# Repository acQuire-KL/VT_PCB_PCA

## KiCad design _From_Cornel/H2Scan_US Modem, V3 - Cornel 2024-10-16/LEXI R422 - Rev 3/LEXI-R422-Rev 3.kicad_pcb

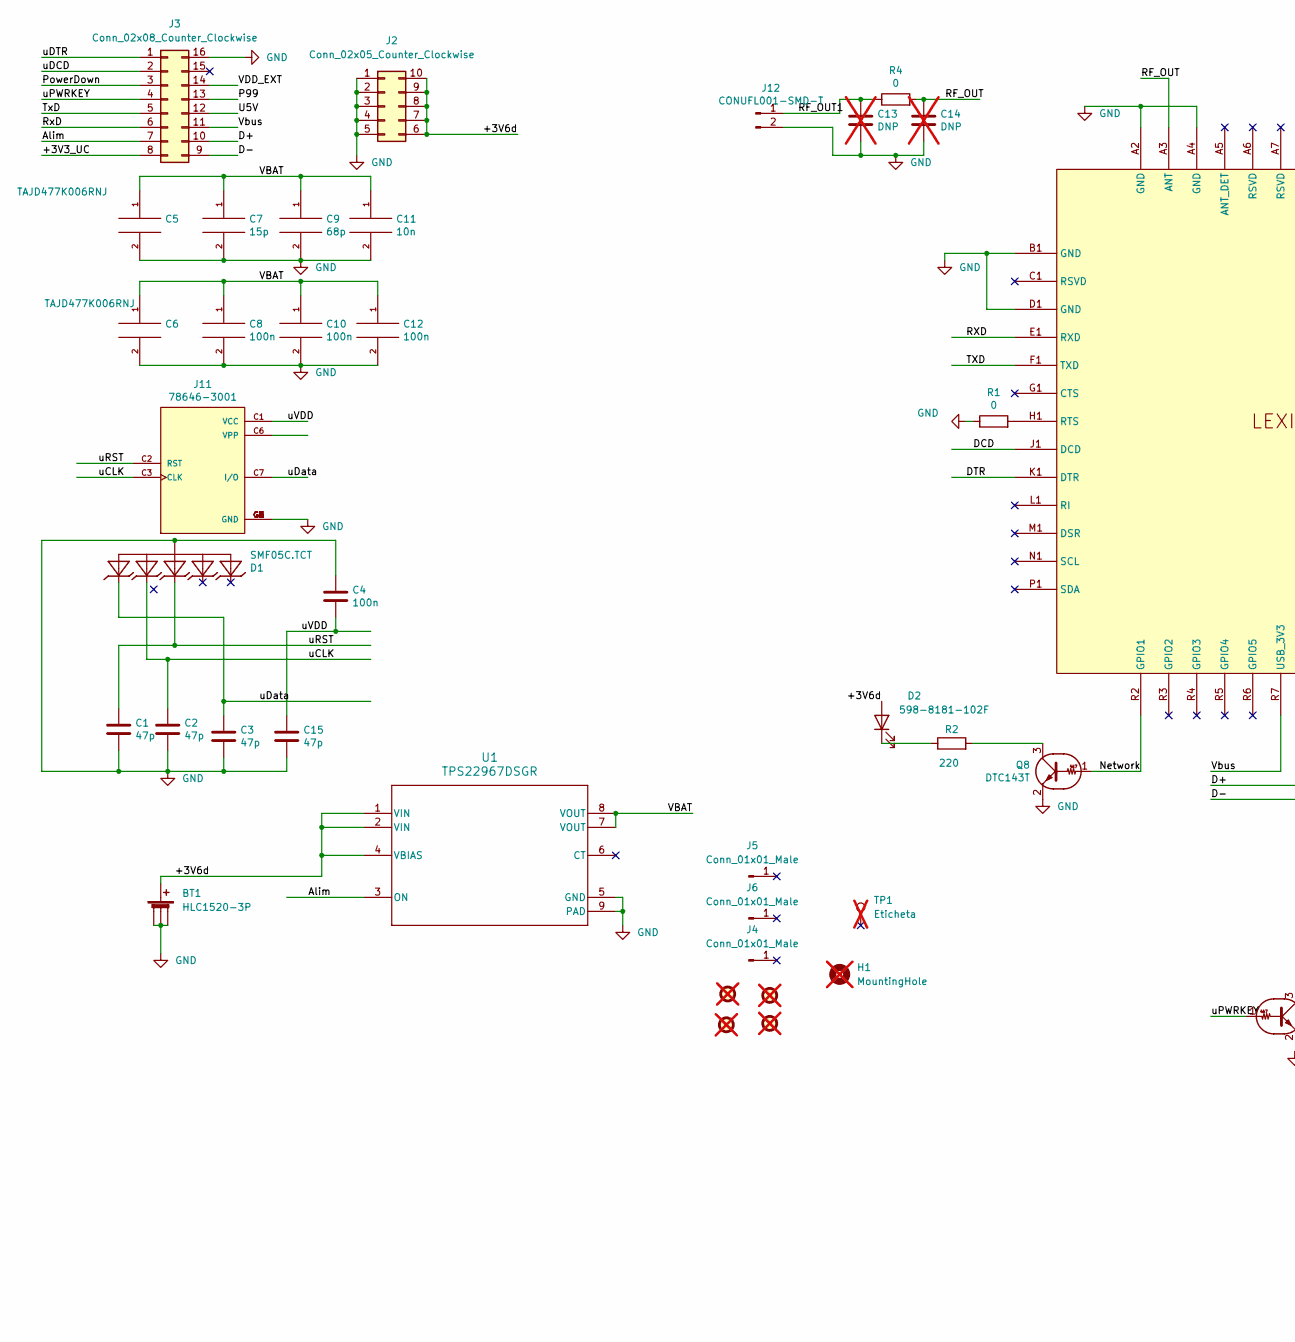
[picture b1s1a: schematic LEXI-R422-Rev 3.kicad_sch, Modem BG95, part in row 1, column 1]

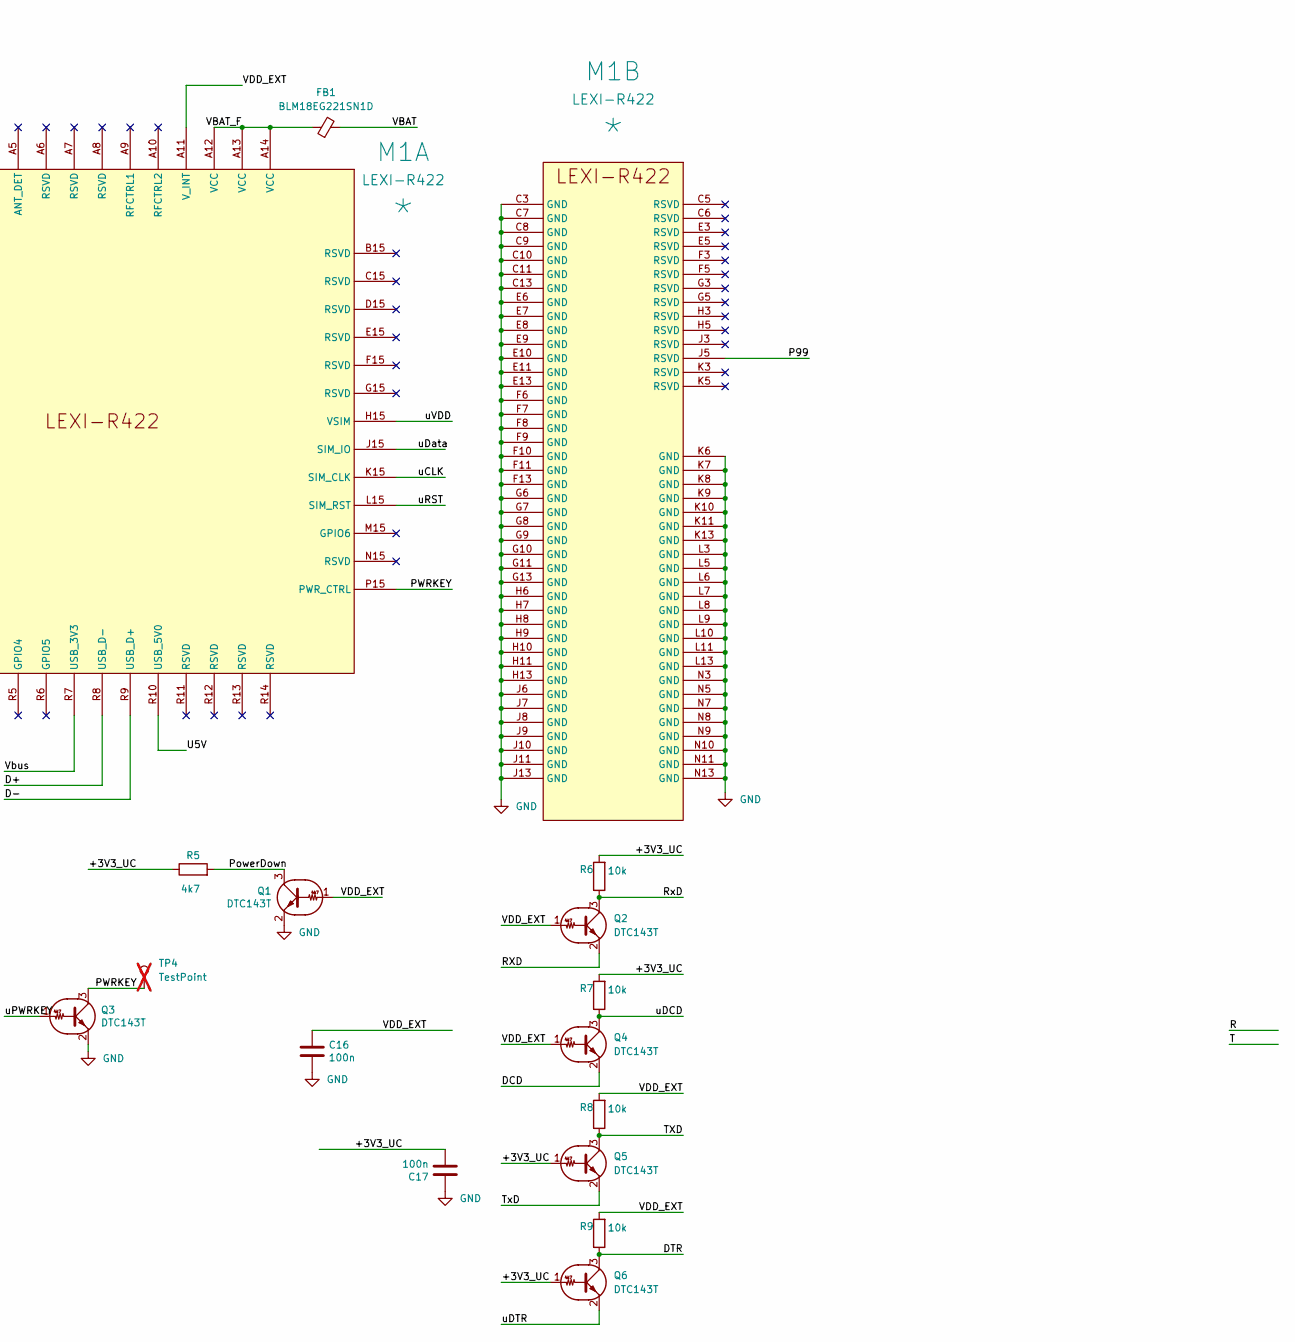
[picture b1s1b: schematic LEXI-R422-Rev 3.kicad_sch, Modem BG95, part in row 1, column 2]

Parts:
BT1: HLC1520-3P
C1, C2, C3, C15: 47p; C_0603_1608Metric
C4, C8, C10, C12, C16, C17: 100n; C_0603_1608Metric
C5, C6: TAJD477K006RNJ; CP_EIA-7361-38_AVX-V_Pad2.18x3.30mm_HandSolder
C7: 15p; C_0603_1608Metric
C9: 68p; C_0603_1608Metric
C11: 10n; C_0603_1608Metric
C13, C14: DNP; C_0603_1608Metric; not fitted
D1: SMF05C.TCT; SC70-6
D2: 598-8181-102F; LED_0805_2012Metric
FB1: BLM18EG221SN1D; L_Walsin_WLFM201209x
FID1, FID2, FID3, FID4: Fiducial; Fiducial_1mm_Mask2mm; not fitted
H1: MountingHole; MountingHole_2.5mm Simpla; not fitted
J2: Conn_02x05_Counter_Clockwise; PinHeader_2x05_P2.54mm_Vertical_SMD_MOD
J3: Conn_02x08_Counter_Clockwise; PinHeader_2x08_P2.54mm_Vertical_SMD_MOD
J4, J5, J6: Conn_01x01_Male; TestPoint_Pad_5.1x5.1mm
J11: 78646-3001; MOLEX_78646-3001; DIGI-KEY_PART_NUMBER WM9364CT-ND
J12: CONUFL001-SMD-T; U.FL_Molex_MCRF_73412-0110_Vertical
M1: LEXI-R422; LEXI; Manufacturer P/N *
Q1, Q2, Q3, Q4, Q5, Q6, Q8: DTC143T; SOT-23
R1, R4: 0; R_0603_1608Metric
R2: 220; R_0603_1608Metric
R5: 4k7; R_0603_1608Metric
R6, R7, R8, R9: 10k; R_0603_1608Metric
TP1: Eticheta; not fitted
TP4: TestPoint; TestPoint_Pad_D1.5mm; not fitted
U1: TPS22967DSGR; WSON-8-1EP_2x2mm_P0.5mm_EP0.9x1.6mm_ThermalVias

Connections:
/+3V3_UC: C17.2, J3.8, Q5.1 (B), Q6.1 (B), R5.1, R6.2, R7.2
/+3V6d: BT1.1 (+), D2.2 (A), J2.6, J2.7, J2.8, J2.9, J2.10, U1.1 (VIN), U1.2 (VIN), U1.4 (VBIAS)
/Alim: J3.7, U1.3 (ON)
/D+: J3.10, M1.R8 (USB_D-)
/D-: J3.9, M1.R9 (USB_D+)
/DCD: M1.J1 (DCD), Q4.2 (E)
/DTR: M1.K1 (DTR), Q6.3 (C), R9.1
/Network: M1.R2 (GPIO1), Q8.1 (B)
/P99: J3.13, M1.J5 (RSVD)
/PWRKEY: M1.P15 (PWR_CTRL), Q3.3 (C), TP4.1
/PowerDown: J3.3, Q1.3 (C), R5.2
/RF_OUT: C14.1, M1.A3 (ANT), R4.2
/RF_OUT1: C13.1, J12.1, R4.1
/RXD: M1.E1 (RXD), Q2.2 (E)
/RxD: J3.6, Q2.3 (C), R6.1
/TXD: M1.F1 (TXD), Q5.3 (C), R8.1
/TxD: J3.5, Q5.2 (E)
/U5V: J3.12, M1.R10 (USB_5V0)
/VBAT: C5.1, C6.1, C7.1, C8.1, C9.1, C10.1, C11.1, C12.1, FB1.2, U1.7 (VOUT), U1.8 (VOUT)
/VBAT_F: FB1.1, M1.A12 (VCC), M1.A13 (VCC), M1.A14 (VCC)
/VDD_EXT: C16.1, J3.14, M1.A11 (V_INT), Q1.1 (B), Q2.1 (B), Q4.1 (B), R8.2, R9.2
/Vbus: J3.11, M1.R7 (USB_3V3)
/uCLK: C2.1, D1.5, J11.C3 (CLK), M1.K15 (SIM_CLK)
/uDCD: J3.2, Q4.3 (C), R7.1
/uDTR: J3.1, Q6.2 (E)
/uData: C3.1, D1.6, J11.C7 (I/O), M1.J15 (SIM_IO)
/uPWRKEY: J3.4, Q3.1 (B)
/uRST: C1.1, D1.4, J11.C2 (RST), M1.L15 (SIM_RST)
/uVDD: C4.2, C15.1, J11.C1 (VCC), M1.H15 (VSIM)
GND: BT1.2 (-), BT1.3 (-), BT1.4 (-), C1.2, C2.2, C3.2, C4.1, C5.2, C6.2, C7.2, C8.2, C9.2, C10.2, C11.2, C12.2, C13.2, C14.2, C15.2, C16.2, C17.1, D1.2, J2.1, J2.2, J2.3, J2.4, J2.5, J3.16, J11.C5 (GND), J11.G1 (GND), J11.G2 (GND), J11.G3 (GND), J11.G4 (GND), J11.G5 (GND), J11.G6 (GND), J12.2, M1.A2 (GND), M1.A4 (GND), M1.B1 (GND), M1.C3 (GND), M1.C7 (GND), M1.C8 (GND), M1.C9 (GND), M1.C10 (GND), M1.C11 (GND), M1.C13 (GND), M1.D1 (GND), M1.E6 (GND), M1.E7 (GND), M1.E8 (GND), M1.E9 (GND), M1.E10 (GND), M1.E11 (GND), M1.E13 (GND), M1.F6 (GND), M1.F7 (GND), M1.F8 (GND), M1.F9 (GND), M1.F10 (GND), M1.F11 (GND), M1.F13 (GND), M1.G6 (GND), M1.G7 (GND), M1.G8 (GND), M1.G9 (GND), M1.G10 (GND), M1.G11 (GND), M1.G13 (GND), M1.H6 (GND), M1.H7 (GND), M1.H8 (GND), M1.H9 (GND), M1.H10 (GND), M1.H11 (GND), M1.H13 (GND), M1.J6 (GND), M1.J7 (GND), M1.J8 (GND), M1.J9 (GND), M1.J10 (GND), M1.J11 (GND), M1.J13 (GND), M1.K6 (GND), M1.K7 (GND), M1.K8 (GND), M1.K9 (GND), M1.K10 (GND), M1.K11 (GND), M1.K13 (GND), M1.L3 (GND), M1.L5 (GND), M1.L6 (GND), M1.L7 (GND), M1.L8 (GND), M1.L9 (GND), M1.L10 (GND), M1.L11 (GND), M1.L13 (GND), M1.N3 (GND), M1.N5 (GND), M1.N7 (GND), M1.N8 (GND), M1.N9 (GND), M1.N10 (GND), M1.N11 (GND), M1.N13 (GND), Q1.2 (E), Q3.2 (E), Q8.2 (E), R1.1, U1.5 (GND), U1.9 (PAD)
unnamed: D2.1 (K), R2.1
unnamed: M1.H1 (RTS), R1.2
unnamed: Q8.3 (C), R2.2

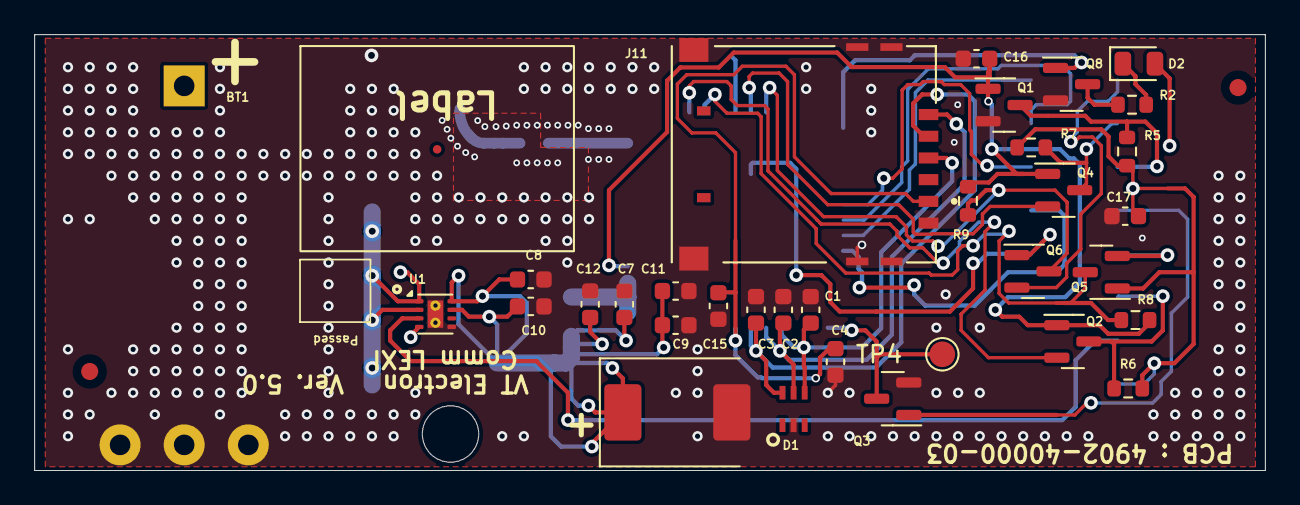
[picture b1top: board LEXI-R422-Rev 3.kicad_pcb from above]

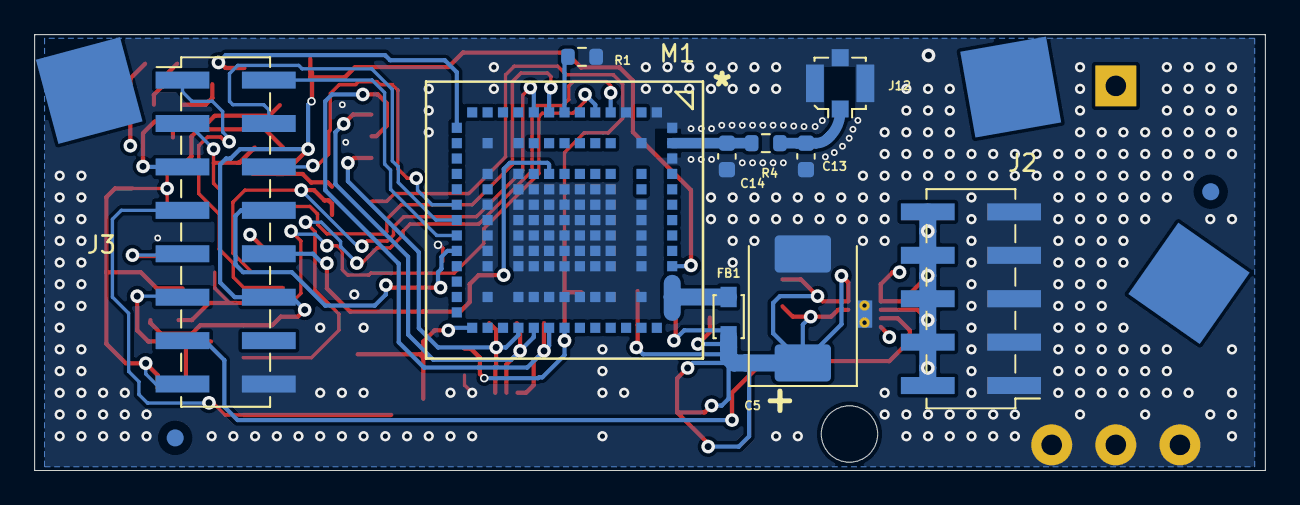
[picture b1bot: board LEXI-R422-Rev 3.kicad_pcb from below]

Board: 4 copper layers, 72.0 x 25.5 mm, 52 parts (15 on the bottom side), 33 nets.

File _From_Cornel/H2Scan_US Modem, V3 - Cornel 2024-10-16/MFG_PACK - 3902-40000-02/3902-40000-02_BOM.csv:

"Reference","Value","Datasheet","Footprint","Qty","DNP","VTPN"
"BT1","HLC1520-3P","~","Battery:HLC1520-3P","1","","4200-00020-00"
"C1,C2,C3,C15","47p","~","Capacitor_SMD:C_0603_1608Metric","4","","4106-00080-00"
"C4,C8,C10,C12,C16,C17","100n","~","Capacitor_SMD:C_0603_1608Metric","6","","4106-00020-00"
"C5,C6","TAJD477K006RNJ","~","Capacitor_Tantalum_SMD:CP_EIA-7361-38_AVX-V_Pad2.18x3.30mm_HandSolder","2","","4128-00100-00"
"C7","15p","~","Capacitor_SMD:C_0603_1608Metric","1","","4106-00070-00"
"C9","68p","~","Capacitor_SMD:C_0603_1608Metric","1","","4106-00060-00"
"C11","10n","~","Capacitor_SMD:C_0603_1608Metric","1","","4106-00015-00"
"C13,C14","DNP","~","Capacitor_SMD:C_0603_1608Metric","2","DNP","4106-00000-00"
"D1","SMF05C.TCT","","Diode_SMD:SC70-6","1","","4724-00010-00"
"D2","598-8181-102F","~","LED_SMD:LED_0805_2012Metric","1","","4752-01010-00"
"FB1","BLM18EG221SN1D","~","Inductor_SMD:L_Walsin_WLFM201209x","1","","4300-01010-00"
"FID1,FID2,FID3,FID4","Fiducial","~","Fiducial:Fiducial_1mm_Mask2mm","4","DNP","4000-00000-00"
"H1","MountingHole","~","MountingHole:MountingHole_2.5mm  Simpla","1","DNP","4000-00000-00"
"J2","Conn_02x05_Counter_Clockwise","~","Connector_PinHeader_2.54mm:PinHeader_2x05_P2.54mm_Vertical_SMD_MOD","1","","4402-00020-00"
"J3","Conn_02x08_Counter_Clockwise","~","Connector_PinHeader_2.54mm:PinHeader_2x08_P2.54mm_Vertical_SMD_MOD","1","","4402-00030-00"
"J4,J5,J6","Conn_01x01_Male","~","TestPoint:TestPoint_Pad_5.1x5.1mm","3","","4753-00010-00"
"J11","78646-3001","","Connector_Molex:MOLEX_78646-3001","1","","4414-00020-00"
"J12","CONUFL001-SMD-T","~","Connector_Coaxial:U.FL_Molex_MCRF_73412-0110_Vertical","1","","4416-00010-00"
"M1","LEXI-R422","","ublox:LEXI","1","","4716-00020-00"
"Q1,Q2,Q3,Q4,Q5,Q6,Q8","DTC143T","","Package_TO_SOT_SMD:SOT-23","7","","4500-00010-00"
"R1,R4","0","~","Resistor_SMD:R_0603_1608Metric","2","","4006-00001-00"
"R2","220","~","Resistor_SMD:R_0603_1608Metric","1","","4006-00020-00"
"R5","4k7","~","Resistor_SMD:R_0603_1608Metric","1","","4006-00150-00"
"R6,R7,R8,R9","10k","~","Resistor_SMD:R_0603_1608Metric","4","","4006-00170-00"
"TP1","Eticheta","~","Symbol:Eticheta","1","DNP","4000-00000-00"
"TP4","TestPoint","~","TestPoint:TestPoint_Pad_D1.5mm","1","DNP","4000-00000-00"
"U1","TPS22967DSGR","TPS22967DSGR","Package_SON:WSON-8-1EP_2x2mm_P0.5mm_EP0.9x1.6mm_ThermalVias","1","","4702-01010-00"

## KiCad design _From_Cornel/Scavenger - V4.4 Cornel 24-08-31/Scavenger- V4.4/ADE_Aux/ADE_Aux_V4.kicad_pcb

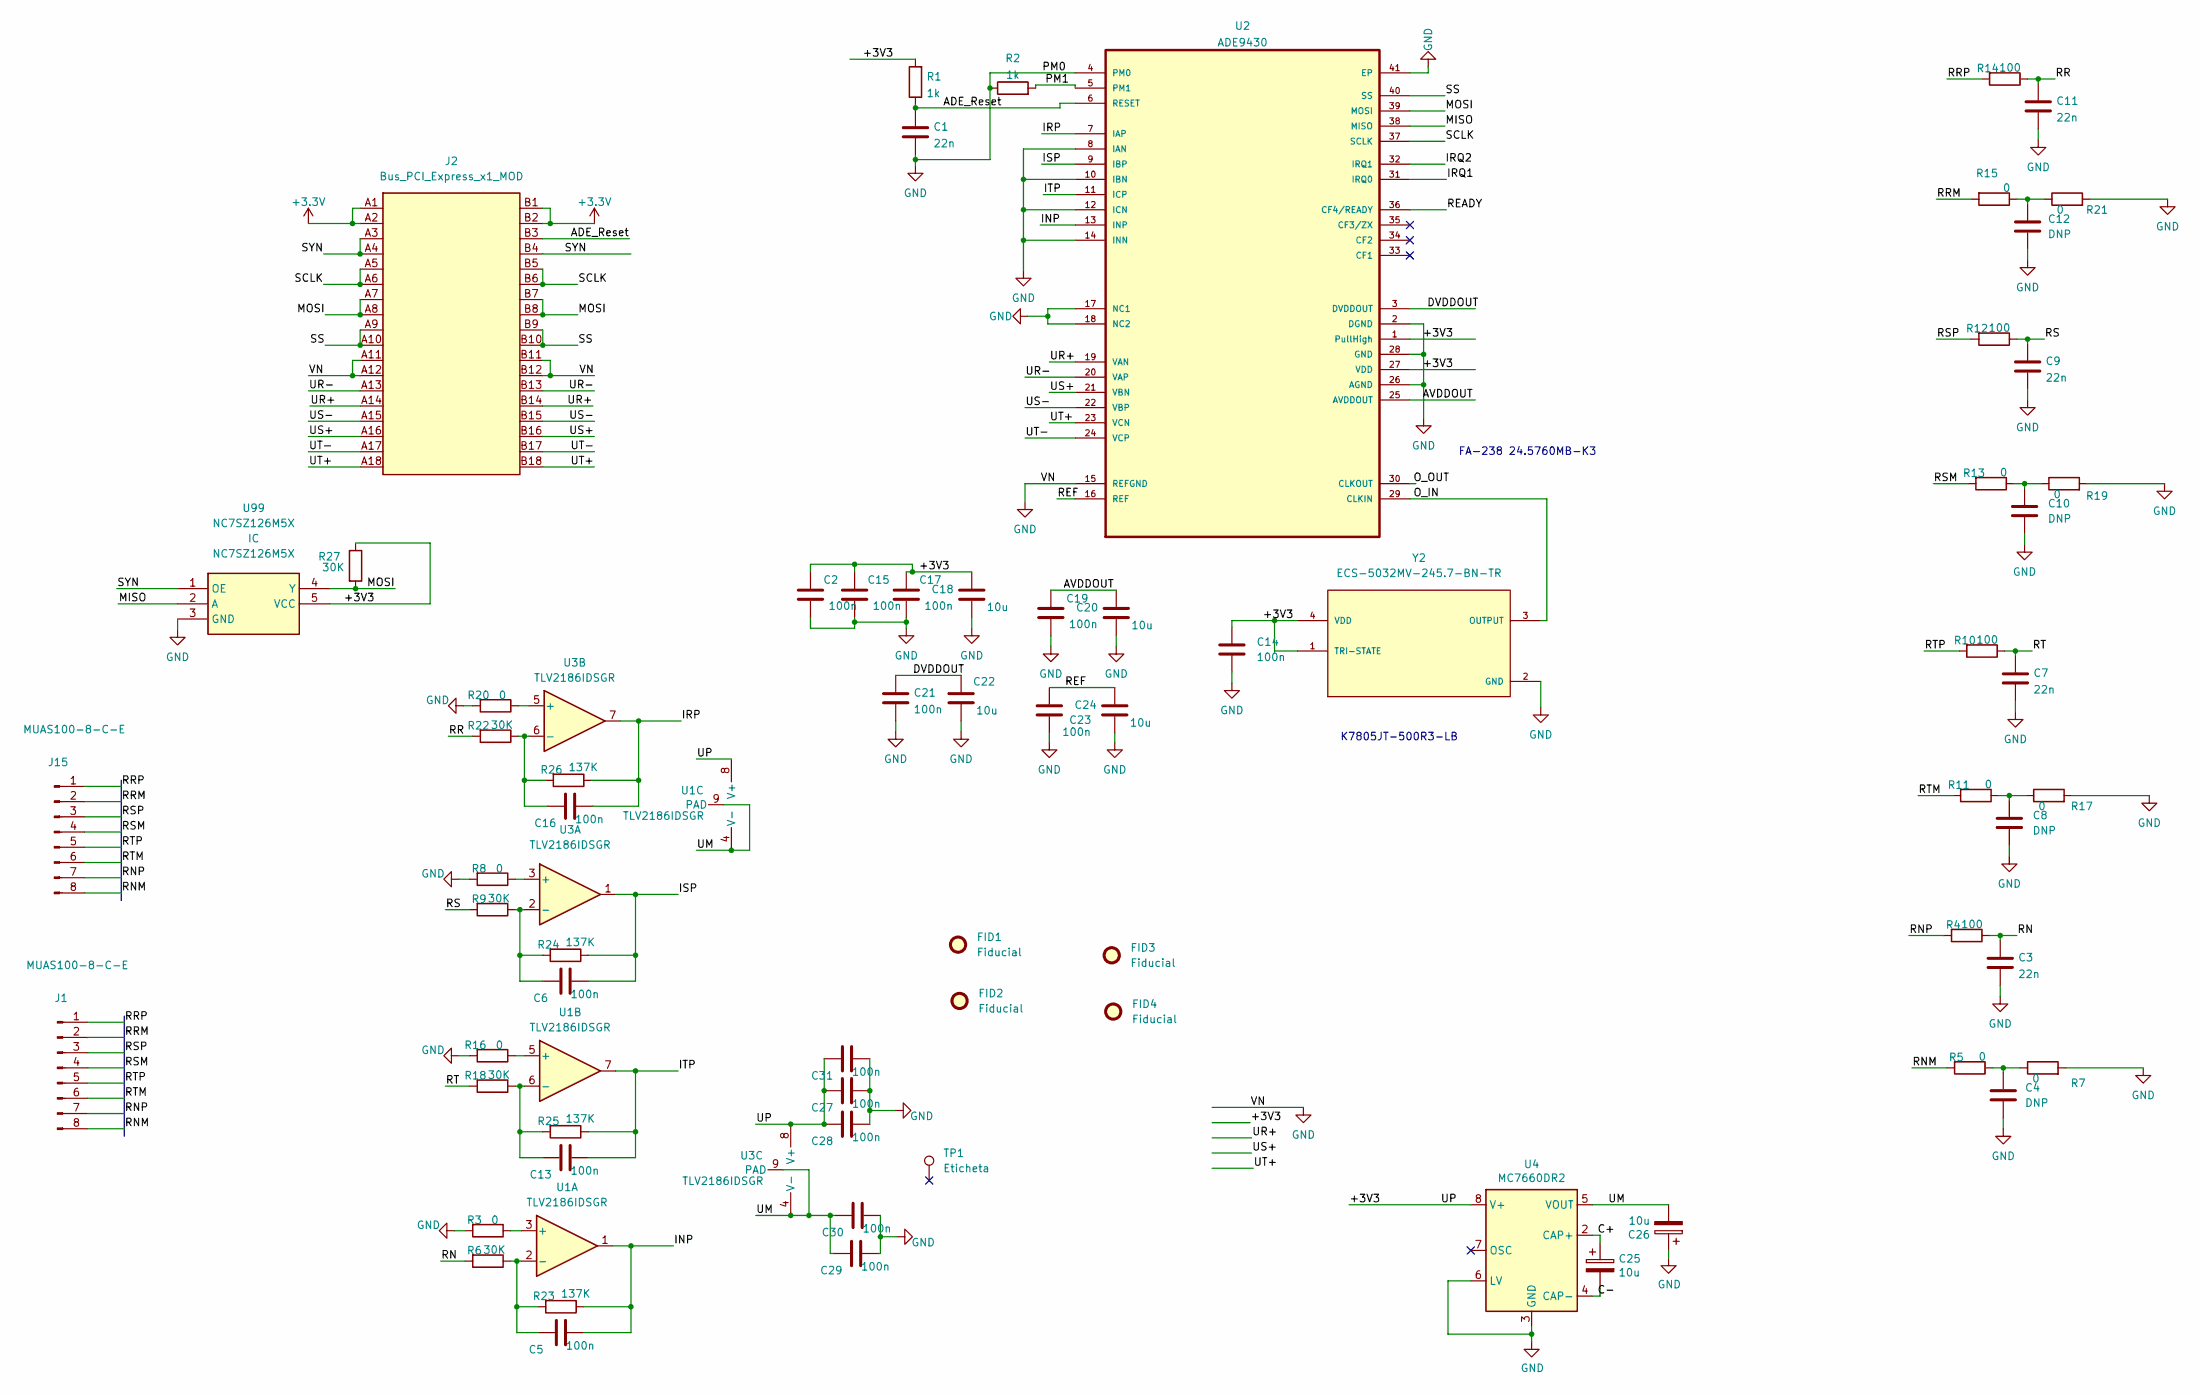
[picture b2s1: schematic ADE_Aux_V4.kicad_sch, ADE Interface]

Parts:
C1, C3, C7, C9, C11: 22n; C_0402_1005Metric
C2: 100n; C_0603_1608Metric
C4, C8, C10, C12: DNP; C_0402_1005Metric
C5, C6, C13, C14, C15, C16, C17, C19, C21, C23, C27, C28, C29, C30, C31: 100n; C_0402_1005Metric
C18, C20, C22, C24, C25, C26: 10u; C_1206_3216Metric
FID1, FID2, FID3, FID4: Fiducial; Fiducial_1mm_Mask2mm
J1: MUAS100-8-C-E; A2501-SR08-XH8AWB
J2: Bus_PCI_Express_x1_MOD; BUS_PCIexpress_x1
J15: MUAS100-8-C-E; PinHeader_1x08_P2.54mm_Vertical
R1, R2: 1k; R_0402_1005Metric
R3, R5, R7, R8, R11, R13, R15, R16, R17, R19, R20, R21: 0; R_0402_1005Metric
R4, R10, R12, R14: 100; R_0402_1005Metric
R6, R9, R18, R22, R27: 30K; R_0402_1005Metric
R23, R24, R25, R26: 137K; R_0402_1005Metric
TP1: Eticheta
U1, U3: TLV2186IDSGR; WSON-8-1EP_2x2mm_P0.5mm_EP0.9x1.6mm_ThermalVias
U2: ADE9430; MPN AD9115BCPZ
U4: MC7660DR2; SO-8_3.9x4.9mm_P1.27mm
U99: NC7SZ126M5X; Buffer3S; Manufacturer_Part_Number NC7SZ126M5X; Mouser Part Number 512-NC7SZ126M5X
Y2: ECS-5032MV-245.7-BN-TR; OSC_ECS-5032MV-245.7-BN-TR

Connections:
/ADE_Reset: C1.1, J2.B3, R1.1, U2.6 (RESET)
/AVDDOUT: C19.1, C20.1, U2.25 (AVDDOUT)
/C+: C25.1, U4.2 (CAP+)
/C-: C25.2, U4.4 (CAP-)
/DVDDOUT: C21.1, C22.1, U2.3 (DVDDOUT)
/INP: C5.1, R23.1, U1.1, U2.13 (INP)
/IRP: C16.1, R26.1, U2.7 (IAP), U3.7
/IRQ1: U2.31 (IRQ0)
/IRQ2: U2.32 (IRQ1)
/ISP: C6.1, R24.1, U2.9 (IBP), U3.1
/ITP: C13.1, R25.1, U1.7, U2.11 (ICP)
/MISO: U2.38 (MISO), U99.2 (A)
/MOSI: J2.A7, J2.A8, J2.B7, J2.B8, R27.2, U2.39 (MOSI), U99.4 (Y)
/O_IN: U2.29 (CLKIN), Y2.3 (OUTPUT)
/O_OUT: U2.30 (CLKOUT)
/PM1: R2.2, U2.5 (PM1)
/READY: U2.36 (CF4/READY)
/REF: C23.1, C24.1, U2.16 (REF)
/RN: C3.1, R4.1, R6.2
/RNM: J1.8, J15.8, R5.2
/RNP: J1.7, J15.7, R4.2
/RR: C11.1, R14.1, R22.2
/RRM: J1.2, J15.2, R15.2
/RRP: J1.1, J15.1, R14.2
/RS: C9.1, R9.2, R12.1
/RSM: J1.4, J15.4, R13.2
/RSP: J1.3, J15.3, R12.2
/RT: C7.1, R10.1, R18.2
/RTM: J1.6, J15.6, R11.2
/RTP: J1.5, J15.5, R10.2
/SCLK: J2.A5, J2.A6, J2.B5, J2.B6, U2.37 (SCLK)
/SS: J2.A9, J2.A10, J2.B9, J2.B10, U2.40 (SS)
/SYN: J2.A3, J2.A4, J2.B4, U99.1 (OE)
/UM: C26.2, C29.2, C30.2, U1.4 (V-), U1.9 (PAD), U3.4 (V-), U3.9 (PAD), U4.5 (VOUT)
/UR+: J2.A14, J2.B14, U2.19 (VAN)
/UR-: J2.A13, J2.B13, U2.20 (VAP)
/US+: J2.A16, J2.B16, U2.21 (VBN)
/US-: J2.A15, J2.B15, U2.22 (VBP)
/UT+: J2.A18, J2.B18, U2.23 (VCN)
/UT-: J2.A17, J2.B17, U2.24 (VCP)
GND: C1.2, C2.2, C3.2, C4.2, C7.2, C8.2, C9.2, C10.2, C11.2, C12.2, C14.2, C15.2, C17.2, C18.2, C19.2, C20.2, C21.2, C22.2, C23.2, C24.2, C26.1, C27.1, C28.1, C29.1, C30.1, C31.1, J2.A11, J2.A12, J2.B11, J2.B12, R2.1, R3.2, R7.2, R8.2, R16.2, R17.2, R19.2, R20.2, R21.2, U2.2 (DGND), U2.4 (PM0), U2.8 (IAN), U2.10 (IBN), U2.12 (ICN), U2.14 (INN), U2.15 (REFGND), U2.17 (NC1), U2.18 (NC2), U2.26 (AGND), U2.28 (GND), U2.41 (EP), U4.3 (GND), U4.6 (LV), U99.3 (GND), Y2.2 (GND)
unnamed: C4.1, R5.1, R7.1
unnamed: C5.2, R6.1, R23.2, U1.2 (-)
unnamed: C6.2, R9.1, R24.2, U3.2 (-)
unnamed: C8.1, R11.1, R17.1
unnamed: C10.1, R13.1, R19.1
unnamed: C12.1, R15.1, R21.1
unnamed: C13.2, R18.1, R25.2, U1.6 (-)
unnamed: C16.2, R22.1, R26.2, U3.6 (-)
unnamed: R3.1, U1.3 (+)
unnamed: R8.1, U3.3 (+)
unnamed: R16.1, U1.5 (+)
unnamed: R20.1, U3.5 (+)

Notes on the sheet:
FA-238 24.5760MB-K3
K7805JT-500R3-LB

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
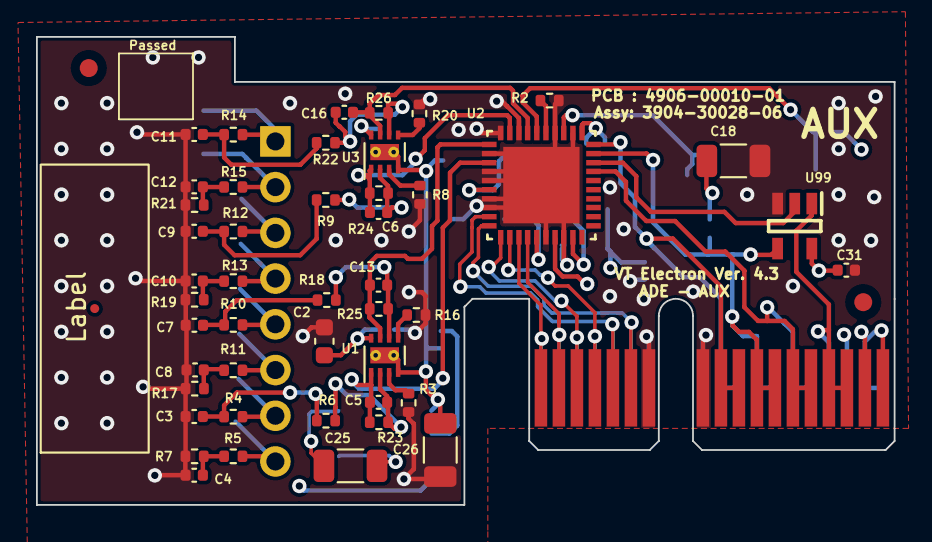
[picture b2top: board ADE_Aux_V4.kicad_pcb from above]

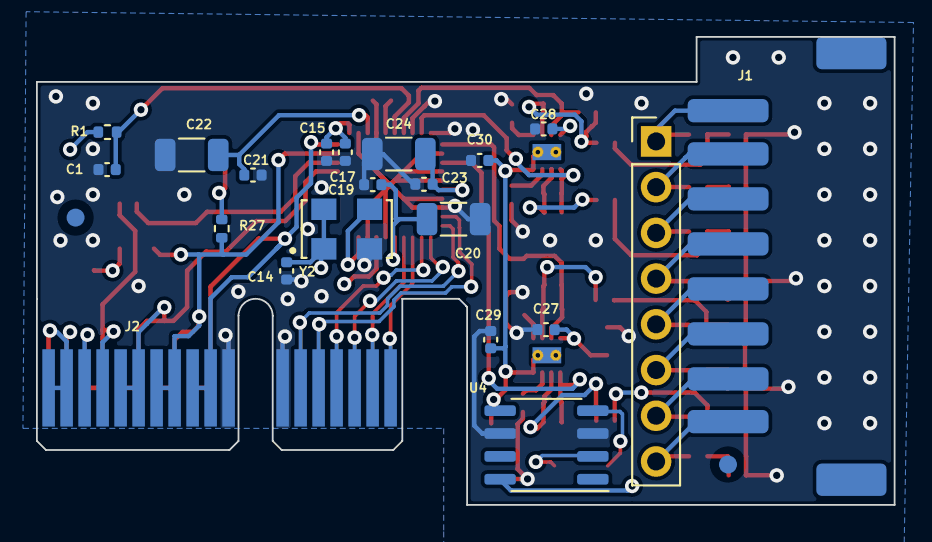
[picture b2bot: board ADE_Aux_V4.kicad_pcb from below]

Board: 4 copper layers, 47.6 x 26.0 mm, 72 parts (23 on the bottom side), 50 nets.

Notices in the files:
parts and their libraries:
Copyright 2021 Accelerated Designs. All rights reserved.
